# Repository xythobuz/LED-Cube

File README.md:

# 8x8x8 LED Cube

8x8x8 Single Color LED Cube built with an AtMega32.

## Building the Software

You need an AVR GCC Toolchain (eg. WinAVR) to compile both AVR firmwares. You need a C Compiler for your computer (only gcc tested, others should work) and a recent JDK with Java3D to build the PC Software, CubeControl. It should work on Windows, Mac OS X and Linux. To compile a project, just enter it's directory and run make. If you get errors compiling CubeControl, try changing the hard-coded JDK paths in the libSerial makefile, found in CubeControl/libSerial.

## Hardware

This LED-Cube uses an AtMega32 for displaying animations and an AtMega8 for Audio Visualizations. I first built the Circuit on a 160x100mm hole-grid board. This was very cumbersome, so I created a dual-sided PCB Layout with SMD Parts. You can find this Layout and the Schematic in the Hardware folder, as PNGs and Eagle files. There's also a partlist.

## Software

### CubeFirmware

CubeFirmware controls the AtMega32, which in turn displays images and communicates over USB. It's in the CubeFirmware folder. Compile with avr-gcc, using the makefile (just run 'make').

### AudioFirmware

This firmware controls the AtMega8, which interfaces the MSGEQ7 to get sound data. It is addressed by the CubeFirmware as a TWI-Slave. Compile it like CubeFirmware.

### CubeControl

CubeControl is a PC software, written in Java and mostly platform-independent, to create Animations for the Cube and send them to it. It depends on [Java3D](http://www.oracle.com/technetwork/java/javase/tech/index-jsp-138252.html) to display a rotatable, clickable 3D View of the LED-Cube. It comes with it's own Serial Library to communicate with the Cube. Compile it with the makefile. You need a working javac and gcc in your Path. To compile under windows get something like [MinGW](http://www.mingw.org/) or try Microsofts compiler.
A more or less recent Version of CubeControl can be found as CubeControl.jar. It includes a Mac and a Windows Version of the serial driver, so it is compatible with both of these platforms.

*Warning:* Java3D 1.5 is incompatible with more recent OS X versions and/or Java 7. [Possible workaround](https://github.com/hharrison/).

Also the Windows build of CubeControl is not tested very thoroughly. If you're on a 64bit Windows, you may also need to modify the libSerial makefile (add the `-m64` flag in the gcc call).

### HardwareEmulator

Allows you to test CubeControls up-/download capabilites. Unix only!

### UploadTest

Allows you to send test data or animations saved by CubeControl to the Cube. Unix only!

## License

See the included LICENSE file. This software is released as GPLv3. It incorporates some code from Peter Danneger (a [button debounce routine](http://www.mikrocontroller.net/articles/Entprellung#Debounce-Makro_von_Peter_Dannegger)) and Peter Fleury ([TWI Library](http://homepage.hispeed.ch/peterfleury/avr-software.html)).

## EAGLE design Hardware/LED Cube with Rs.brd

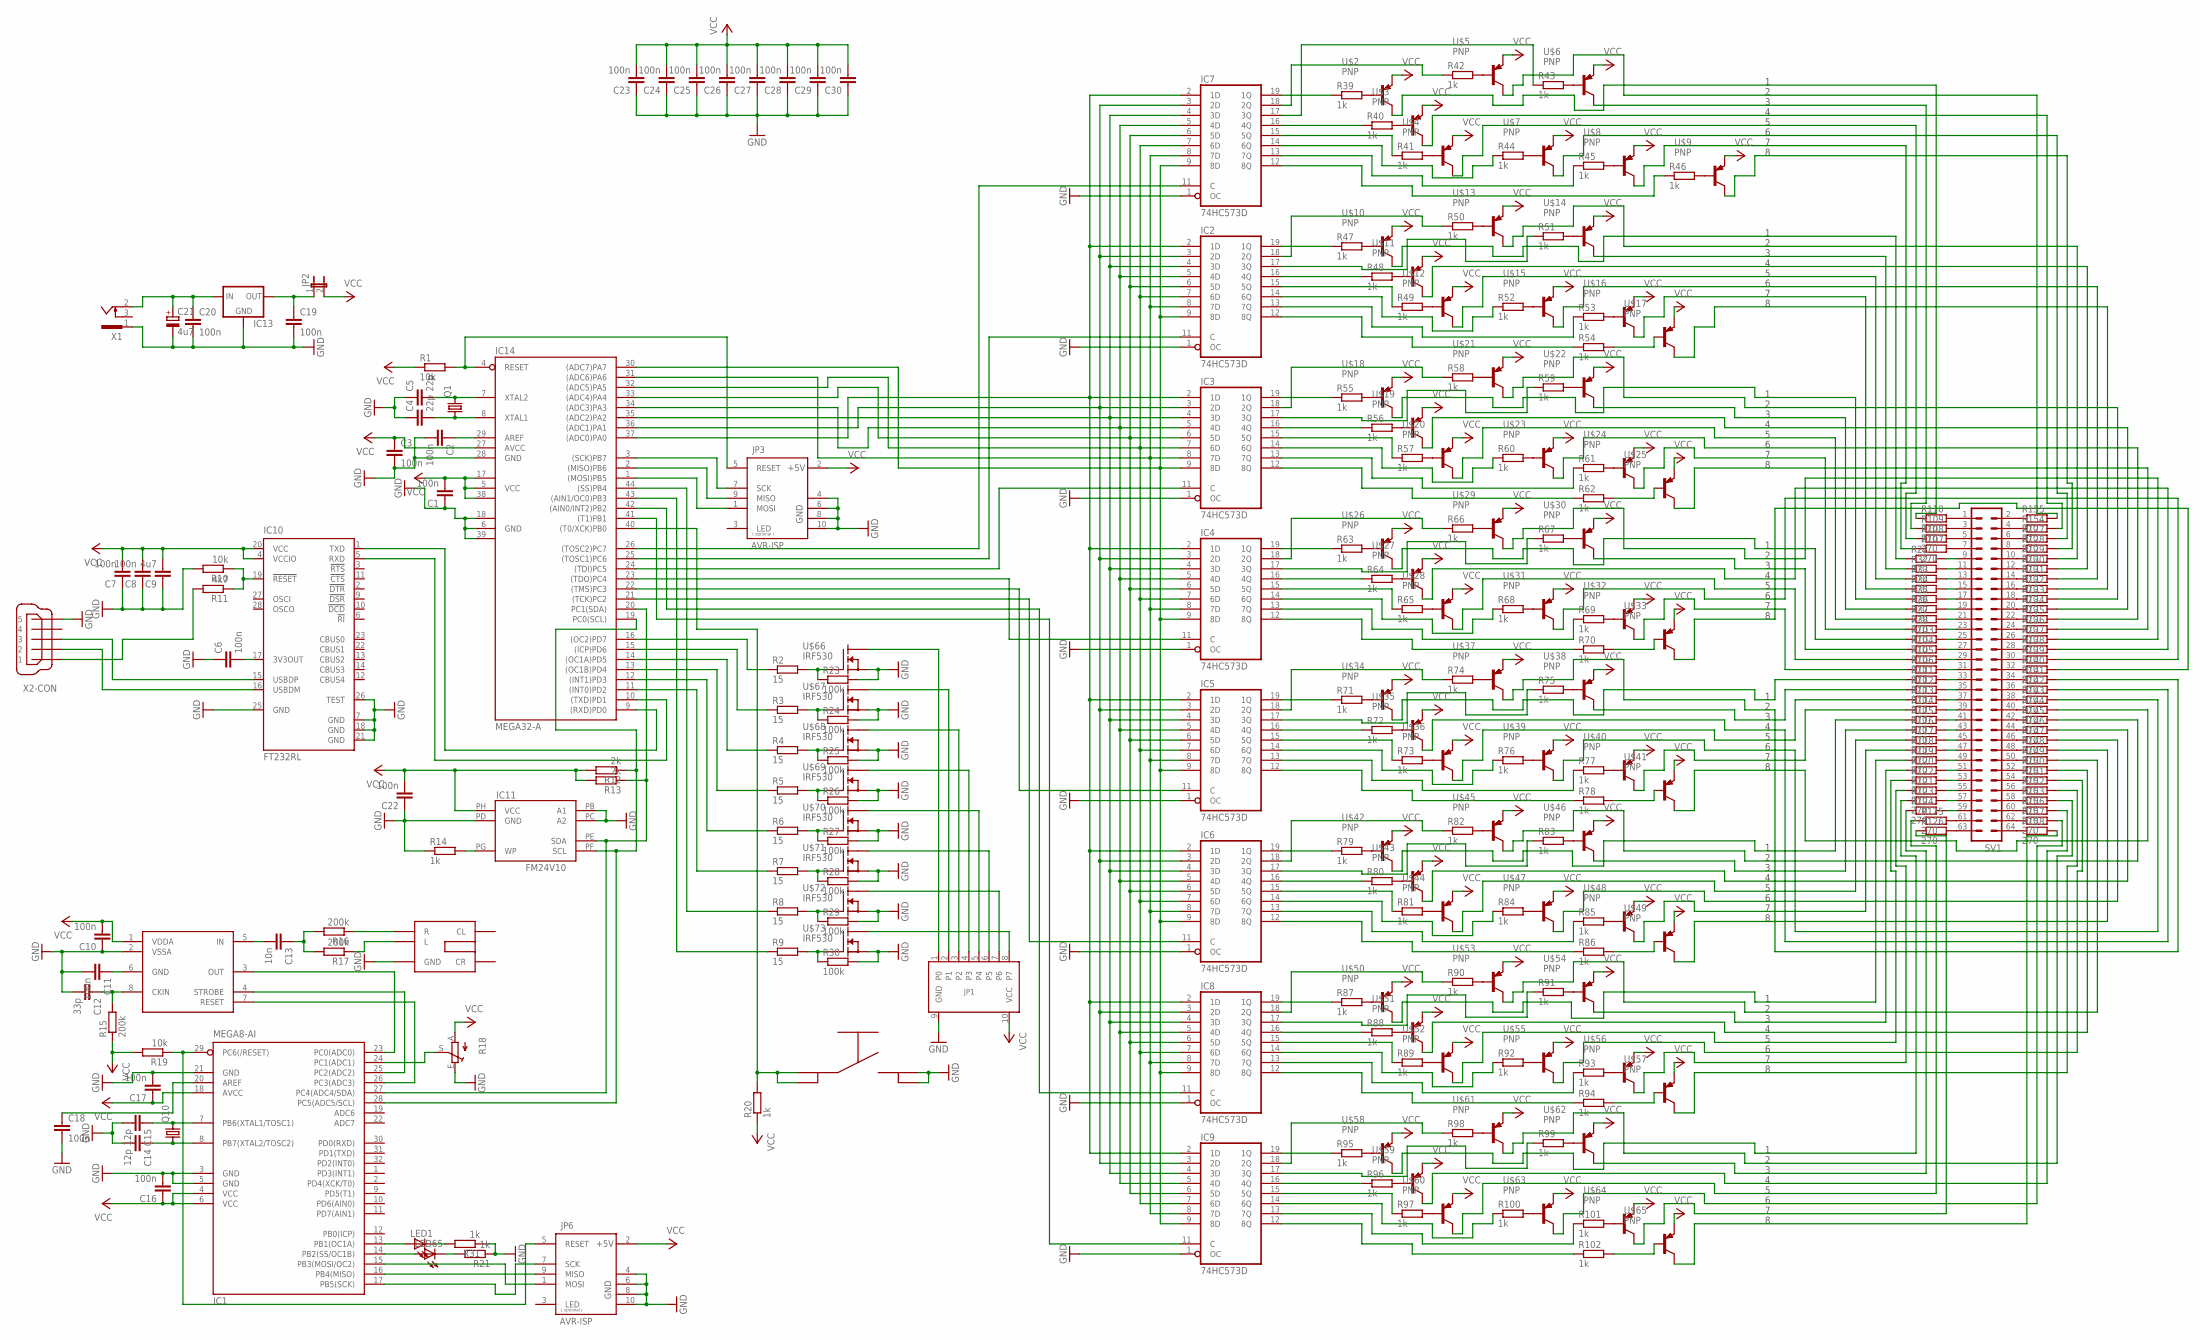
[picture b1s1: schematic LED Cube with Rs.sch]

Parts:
C1, C2, C3, C6, C7, C8, C10, C11, C16, C17, C18, C19, C20, C22, C23, C24, C25, C26, C27, C28, C29, C30: 100n; C0603
C4, C5: 22p; C0603
C9: 4u7; C0603
C12: 33p; C0603
C13: 10n; C0603
C14, C15: 12p; C0603
C21: 4u7; TAP5-80
IC1: MEGA8-AI; TQFP32-08
IC2, IC3, IC4, IC5, IC6, IC7, IC8, IC9: 74HC573D; SO20W
IC10: FT232RL; SSOP28
IC11: FM24V10; SOIC8
IC12: MSGEQ7; DIP8
IC13: 78XXS
IC14: MEGA32-A; TQFP44
JP1: PORT; ML10
JP2: JP1E; JP1
JP3, JP6: AVR-ISP; ML10
LED1, LED65: LEDCHIPLED_0603; CHIPLED_0603
Q1, Q10: CRYSTALHC49S; HC49/S
R1, R10, R19: 10k; R0603
R2, R3, R4, R5, R6, R7, R8, R9: 15; R0603
R11: 4k7; R0603
R12, R13: 2k; R0603
R14, R20, R21, R31, R39, R40, R41, R42, R43, R44, R45, R46, R47, R48, R49, R50, R51, R52, R53, R54, R55, R56, R57, R58, R59, R60, R61, R62, R63, R64, R65, R66, R67, R68, R69, R70, R71, R72, R73, R74, R75, R76, R77, R78, R79, R80, R81, R82, R83, R84, R85, R86, R87, R88, R89, R90, R91, R92, R93, R94, R95, R96, R97, R98, R99, R100, R101, R102: 1k; R0603
R15, R16, R17: 200k; R0603
R18: TRIM_EU-PT10S; PT-10S
R22, R32, R33, R34, R35, R36, R37, R38, R103, R104, R105, R106, R107, R108, R109, R110, R111, R112, R113, R114, R115, R116, R117, R118, R119, R120, R121, R122, R123, R124, R125, R126, R127, R128, R129, R130, R131, R132, R133, R134, R135, R136, R137, R138, R139, R140, R141, R142, R143, R144, R145, R146, R147, R148, R149, R150, R151, R152, R153, R154, R155, R156, R157, R158: 270; R0603
R23, R24, R25, R26, R27, R28, R29, R30: 100k; R0603
SV1: ML64
U$1: KLINKENBUCHSE; KLINKEPRINT
U$2, U$3, U$4, U$5, U$6, U$7, U$8, U$9, U$10, U$11, U$12, U$13, U$14, U$15, U$16, U$17, U$18, U$19, U$20, U$21, U$22, U$23, U$24, U$25, U$26, U$27, U$28, U$29, U$30, U$31, U$32, U$33, U$34, U$35, U$36, U$37, U$38, U$39, U$40, U$41, U$42, U$43, U$44, U$45, U$46, U$47, U$48, U$49, U$50, U$51, U$52, U$53, U$54, U$55, U$56, U$57, U$58, U$59, U$60, U$61, U$62, U$63, U$64, U$65: PNP; SOT323
U$66, U$67, U$68, U$69, U$70, U$71, U$72, U$73: IRF530; TO220-3V
U$74: TASTER; SMDTASTER
X1: 733980-62
X2: USB-B-MINI-SMD

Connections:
GND: C1.1, C2.2, C3.2, C4.1, C5.1, C6.1, C7.1, C8.1, C9.1, C10.1, C11.2, C12.2, C14.2, C15.2, C16.2, C17.2, C18.2, C19.2, C20.2, C21.-, C22.1, C23.1, C24.1, C25.1, C26.1, C27.1, C28.1, C29.1, C30.1, IC1.3 (GND), IC1.5 (GND), IC1.21 (GND), IC2.1 (OC), IC2.10 (GND), IC3.1 (OC), IC3.10 (GND), IC4.1 (OC), IC4.10 (GND), IC5.1 (OC), IC5.10 (GND), IC6.1 (OC), IC6.10 (GND), IC7.1 (OC), IC7.10 (GND), IC8.1 (OC), IC8.10 (GND), IC9.1 (OC), IC9.10 (GND), IC10.7 (GND), IC10.18 (GND), IC10.21 (GND), IC10.25 (GND), IC10.26 (TEST), IC11.PB (A1), IC11.PC (A2), IC11.PD (GND), IC12.2 (VSSA), IC13.GND, IC14.6 (GND), IC14.18 (GND1), IC14.28 (GND), IC14.39 (GND2), JP1.9 (GND), JP3.4 (GND), JP3.6 (GND), JP3.8 (GND), JP3.10 (GND), JP6.4 (GND), JP6.6 (GND), JP6.8 (GND), JP6.10 (GND), R10.2, R14.1, R18.E, R21.1, R23.2, R24.2, R25.2, R26.2, R27.2, R28.2, R29.2, R30.2, R31.1, U$1.GND, U$66.3 (S), U$67.3 (S), U$68.3 (S), U$69.3 (S), U$70.3 (S), U$71.3 (S), U$72.3 (S), U$73.3 (S), U$74.B, U$74.B2, X1.1, X2.5
unnamed: R154.2, U$3.P$3 (C)
unnamed: IC14.4 (RESET), JP3.5 (RESET), R1.2
unnamed: C2.1, IC14.29 (AREF)
unnamed: IC2.2 (1D), IC3.2 (1D), IC4.2 (1D), IC5.2 (1D), IC6.2 (1D), IC7.2 (1D), IC8.2 (1D), IC9.2 (1D), IC14.37 ((ADC0)PA0)
unnamed: IC2.3 (2D), IC3.3 (2D), IC4.3 (2D), IC5.3 (2D), IC6.3 (2D), IC7.3 (2D), IC8.3 (2D), IC9.3 (2D), IC14.36 ((ADC1)PA1)
unnamed: IC2.4 (3D), IC3.4 (3D), IC4.4 (3D), IC5.4 (3D), IC6.4 (3D), IC7.4 (3D), IC8.4 (3D), IC9.4 (3D), IC14.35 ((ADC2)PA2)
unnamed: C5.2, IC14.7 (XTAL2), Q1.2
unnamed: C4.2, IC14.8 (XTAL1), Q1.1
unnamed: IC2.5 (4D), IC3.5 (4D), IC4.5 (4D), IC5.5 (4D), IC6.5 (4D), IC7.5 (4D), IC8.5 (4D), IC9.5 (4D), IC14.34 ((ADC3)PA3)
unnamed: IC2.6 (5D), IC3.6 (5D), IC4.6 (5D), IC5.6 (5D), IC6.6 (5D), IC7.6 (5D), IC8.6 (5D), IC9.6 (5D), IC14.33 ((ADC4)PA4)
unnamed: IC2.7 (6D), IC3.7 (6D), IC4.7 (6D), IC5.7 (6D), IC6.7 (6D), IC7.7 (6D), IC8.7 (6D), IC9.7 (6D), IC14.32 ((ADC5)PA5)
unnamed: IC2.8 (7D), IC3.8 (7D), IC4.8 (7D), IC5.8 (7D), IC6.8 (7D), IC7.8 (7D), IC8.8 (7D), IC9.8 (7D), IC14.31 ((ADC6)PA6)
unnamed: IC2.9 (8D), IC3.9 (8D), IC4.9 (8D), IC5.9 (8D), IC6.9 (8D), IC7.9 (8D), IC8.9 (8D), IC9.9 (8D), IC14.30 ((ADC7)PA7)
unnamed: IC9.11 (C), IC14.41 ((T1)PB1)
unnamed: IC8.11 (C), IC14.42 ((AIN0/INT2)PB2)
unnamed: IC6.11 (C), IC14.21 ((TCK)PC2)
unnamed: IC5.11 (C), IC14.22 ((TMS)PC3)
unnamed: IC4.11 (C), IC14.23 ((TDO)PC4)
unnamed: IC3.11 (C), IC14.24 ((TDI)PC5)
unnamed: IC2.11 (C), IC14.25 ((TOSC1)PC6)
unnamed: IC7.11 (C), IC14.26 ((TOSC2)PC7)
unnamed: R2.2, R23.1, U$66.1 (G)
unnamed: IC14.16 ((OC2)PD7), R2.1
unnamed: IC14.15 ((ICP)PD6), R3.1
unnamed: IC14.14 ((OC1A)PD5), R4.1
unnamed: IC14.13 ((OC1B)PD4), R5.1
unnamed: IC14.12 ((INT1)PD3), R6.1
unnamed: IC14.11 ((INT0)PD2), R7.1
unnamed: IC14.44 ((SS)PB4), R8.1
unnamed: IC14.43 ((AIN1/OC0)PB3), R9.1
unnamed: R3.2, R24.1, U$67.1 (G)
unnamed: R4.2, R25.1, U$68.1 (G)
unnamed: R5.2, R26.1, U$69.1 (G)
unnamed: R6.2, R27.1, U$70.1 (G)
unnamed: R7.2, R28.1, U$71.1 (G)
unnamed: R8.2, R29.1, U$72.1 (G)
unnamed: R9.2, R30.1, U$73.1 (G)
unnamed: JP1.1 (P0), U$66.2 (D)
unnamed: JP1.2 (P1), U$67.2 (D)
unnamed: R106.2, SV1.31
unnamed: R105.2, SV1.29
unnamed: JP1.5 (P4), U$70.2 (D)
unnamed: JP1.6 (P5), U$71.2 (D)
unnamed: JP1.7 (P6), U$72.2 (D)
unnamed: JP1.8 (P7), U$73.2 (D)
unnamed: R11.2, X2.1
unnamed: IC14.3 ((SCK)PB7), JP3.7 (SCK)
unnamed: IC14.2 ((MISO)PB6), JP3.9 (MISO)
unnamed: IC14.1 ((MOSI)PB5), JP3.1 (MOSI)
unnamed: IC10.5 (RXD), IC14.10 ((TXD)PD1)
unnamed: IC10.1 (TXD), IC14.9 ((RXD)PD0)
unnamed: IC10.19 (!RESET), R10.1, R11.1
unnamed: IC1.27 (PC4(ADC4/SDA)), IC11.PE (SDA), IC14.20 (PC1(SDA)), R13.1
unnamed: IC10.15 (USBDP), X2.3
unnamed: C6.2, IC10.17 (3V3OUT)
unnamed: IC10.16 (USBDM), X2.2
unnamed: IC1.28 (PC5(ADC5/SCL)), IC11.PF (SCL), IC14.19 (PC0(SCL)), R12.1
unnamed: IC11.PG (WP), R14.2
unnamed: C12.1, IC12.8 (CKIN), R15.2
unnamed: C11.1, IC12.6 (GND)
unnamed: C13.2, IC12.5 (IN)
unnamed: C13.1, R16.2, R17.2
unnamed: R16.1, U$1.RIGHT (R)
unnamed: R17.1, U$1.LEFT (L)
unnamed: IC1.23 (PC0(ADC0)), IC12.3 (OUT)
unnamed: IC1.29 (PC6(/RESET)), JP6.5 (RESET), R19.1
unnamed: IC1.25 (PC2(ADC2)), IC12.4 (STROBE)
unnamed: IC1.26 (PC3(ADC3)), IC12.7 (RESET)
unnamed: IC14.40 ((T0/XCK)PB0), R20.2, U$74.A, U$74.A2
unnamed: C14.1, IC1.8 (PB7(XTAL2/TOSC2)), Q10.1
unnamed: C15.1, IC1.7 (PB6(XTAL1/TOSC1)), Q10.2
unnamed: R104.2, SV1.27
unnamed: R103.2, SV1.25
unnamed: C20.1, C21.+, IC13.IN, X1.2
unnamed: IC1.14 (PB2(SS/OC1B)), LED65.A
unnamed: LED65.C, R21.2
unnamed: IC1.24 (PC1(ADC1)), R18.S
unnamed: C18.1, IC1.20 (AREF)
unnamed: IC1.16 (PB4(MISO)), JP6.9 (MISO)
unnamed: IC1.15 (PB3(MOSI/OC2)), JP6.1 (MOSI)
unnamed: IC1.17 (PB5(SCK)), JP6.7 (SCK)
unnamed: LED1.C, R31.2
unnamed: IC1.13 (PB1(OC1A)), LED1.A
unnamed: C19.1, IC13.OUT, JP2.1
unnamed: R38.2, SV1.23
unnamed: R37.2, SV1.21
unnamed: R36.2, SV1.19
unnamed: R35.2, SV1.17
unnamed: R34.2, SV1.15
unnamed: R33.2, SV1.13
unnamed: R32.2, SV1.11
unnamed: R22.2, SV1.9
unnamed: R107.2, SV1.7
unnamed: R108.2, SV1.5
unnamed: R123.2, SV1.57
unnamed: R109.2, SV1.3
unnamed: R110.2, SV1.1
unnamed: R155.2, U$5.P$3 (C)
unnamed: R109.1, U$6.P$3 (C)
unnamed: R108.1, U$4.P$3 (C)
unnamed: R44.2, U$7.P$1 (B)
unnamed: R127.2, U$7.P$3 (C)
unnamed: R42.2, U$5.P$1 (B)
unnamed: R128.2, U$9.P$3 (C)
unnamed: R132.2, U$17.P$3 (C)
unnamed: R63.2, U$26.P$1 (B)
unnamed: R64.2, U$27.P$1 (B)
unnamed: R65.2, U$28.P$1 (B)
unnamed: R130.2, U$11.P$3 (C)
unnamed: R129.2, U$13.P$3 (C)
unnamed: R22.1, U$10.P$3 (C)
unnamed: R54.2, U$17.P$1 (B)
unnamed: IC4.19 (1Q), R63.1
unnamed: IC4.16 (4Q), R64.1
unnamed: R66.2, U$29.P$1 (B)
unnamed: IC4.18 (2Q), R66.1
unnamed: R67.2, U$30.P$1 (B)
unnamed: IC4.17 (3Q), R67.1
unnamed: IC4.15 (5Q), R65.1
unnamed: R68.2, U$31.P$1 (B)
unnamed: R71.2, U$34.P$1 (B)
unnamed: R72.2, U$35.P$1 (B)
unnamed: R73.2, U$36.P$1 (B)
unnamed: IC5.19 (1Q), R71.1
unnamed: IC5.16 (4Q), R72.1
unnamed: R74.2, U$37.P$1 (B)
unnamed: IC5.18 (2Q), R74.1
unnamed: R75.2, U$38.P$1 (B)
unnamed: IC7.19 (1Q), R39.1
unnamed: R126.1, U$64.P$3 (C)
unnamed: R125.1, U$60.P$3 (C)
unnamed: IC7.16 (4Q), R40.1
unnamed: IC2.19 (1Q), R47.1
unnamed: R157.2, U$63.P$3 (C)
unnamed: IC2.16 (4Q), R48.1
unnamed: R153.2, U$61.P$3 (C)
unnamed: R95.2, U$58.P$1 (B)
unnamed: R121.1, U$56.P$3 (C)
unnamed: R96.2, U$59.P$1 (B)
unnamed: R97.2, U$60.P$1 (B)
unnamed: IC9.19 (1Q), R95.1
unnamed: R151.2, U$55.P$3 (C)
unnamed: IC9.16 (4Q), R96.1
unnamed: R149.2, U$53.P$3 (C)
unnamed: R87.2, U$50.P$1 (B)
unnamed: R88.2, U$51.P$1 (B)
unnamed: R89.2, U$52.P$1 (B)
unnamed: IC8.16 (4Q), R88.1
unnamed: IC8.19 (1Q), R87.1
unnamed: R90.2, U$53.P$1 (B)
unnamed: IC8.18 (2Q), R90.1
unnamed: R91.2, U$54.P$1 (B)
unnamed: R79.2, U$42.P$1 (B)
unnamed: R80.2, U$43.P$1 (B)
unnamed: R81.2, U$44.P$1 (B)
unnamed: IC6.19 (1Q), R79.1
unnamed: IC6.16 (4Q), R80.1
unnamed: R82.2, U$45.P$1 (B)
unnamed: IC6.18 (2Q), R82.1
unnamed: R83.2, U$46.P$1 (B)
unnamed: R40.2, U$3.P$1 (B)
unnamed: R39.2, U$2.P$1 (B)
unnamed: IC7.15 (5Q), R41.1
unnamed: R110.1, U$2.P$3 (C)
unnamed: R41.2, U$4.P$1 (B)
unnamed: R107.1, U$8.P$3 (C)
unnamed: IC3.19 (1Q), R55.1
unnamed: IC3.16 (4Q), R56.1
unnamed: R47.2, U$10.P$1 (B)
unnamed: IC7.14 (6Q), R44.1
unnamed: R45.2, U$8.P$1 (B)
unnamed: IC7.18 (2Q), R42.1
unnamed: R43.2, U$6.P$1 (B)
unnamed: R48.2, U$11.P$1 (B)
unnamed: IC7.17 (3Q), R43.1
unnamed: IC7.13 (7Q), R45.1
unnamed: R46.2, U$9.P$1 (B)
unnamed: R49.2, U$12.P$1 (B)
unnamed: IC7.12 (8Q), R46.1
unnamed: R35.1, U$18.P$3 (C)
unnamed: R103.1, U$26.P$3 (C)
unnamed: IC4.14 (6Q), R68.1
unnamed: R33.1, U$12.P$3 (C)
unnamed: R50.2, U$13.P$1 (B)
unnamed: IC2.18 (2Q), R50.1
unnamed: R51.2, U$14.P$1 (B)
unnamed: IC2.17 (3Q), R51.1
unnamed: R32.1, U$14.P$3 (C)
unnamed: IC2.15 (5Q), R49.1
unnamed: R69.2, U$32.P$1 (B)
unnamed: IC4.13 (7Q), R69.1
unnamed: R52.2, U$15.P$1 (B)
unnamed: IC2.14 (6Q), R52.1
unnamed: R131.2, U$15.P$3 (C)
unnamed: R53.2, U$16.P$1 (B)
unnamed: IC2.13 (7Q), R53.1
unnamed: R34.1, U$16.P$3 (C)
unnamed: IC4.12 (8Q), R70.1
unnamed: R140.2, U$33.P$3 (C)
unnamed: IC2.12 (8Q), R54.1
unnamed: R55.2, U$18.P$1 (B)
unnamed: R56.2, U$19.P$1 (B)
unnamed: R57.2, U$20.P$1 (B)
unnamed: R111.1, U$34.P$3 (C)
unnamed: R115.1, U$42.P$3 (C)
unnamed: R58.2, U$21.P$1 (B)
unnamed: IC3.18 (2Q), R58.1
unnamed: R59.2, U$22.P$1 (B)
unnamed: IC3.17 (3Q), R59.1
unnamed: IC3.15 (5Q), R57.1
unnamed: R60.2, U$23.P$1 (B)
unnamed: IC3.14 (6Q), R60.1
unnamed: R61.2, U$24.P$1 (B)
unnamed: IC3.13 (7Q), R61.1
unnamed: IC3.12 (8Q), R62.1
unnamed: R136.2, U$25.P$3 (C)
unnamed: R38.1, U$24.P$3 (C)
unnamed: R135.2, U$23.P$3 (C)
unnamed: R37.1, U$20.P$3 (C)
unnamed: R134.2, U$19.P$3 (C)
unnamed: R133.2, U$21.P$3 (C)
unnamed: R119.1, U$50.P$3 (C)
unnamed: R62.2, U$25.P$1 (B)
unnamed: R36.1, U$22.P$3 (C)
unnamed: R106.1, U$32.P$3 (C)
unnamed: R139.2, U$31.P$3 (C)
unnamed: R105.1, U$28.P$3 (C)
unnamed: R138.2, U$27.P$3 (C)
unnamed: R137.2, U$29.P$3 (C)
unnamed: R123.1, U$58.P$3 (C)
unnamed: R70.2, U$33.P$1 (B)
unnamed: R104.1, U$30.P$3 (C)
unnamed: IC5.17 (3Q), R75.1
unnamed: IC5.15 (5Q), R73.1
unnamed: R76.2, U$39.P$1 (B)
unnamed: IC5.14 (6Q), R76.1
unnamed: R77.2, U$40.P$1 (B)
unnamed: IC5.13 (7Q), R77.1
unnamed: IC5.12 (8Q), R78.1
unnamed: R144.2, U$41.P$3 (C)
unnamed: R114.1, U$40.P$3 (C)
unnamed: R143.2, U$39.P$3 (C)
unnamed: R113.1, U$36.P$3 (C)
unnamed: R142.2, U$35.P$3 (C)
unnamed: R141.2, U$37.P$3 (C)
unnamed: R111.2, SV1.33
unnamed: R78.2, U$41.P$1 (B)
unnamed: R112.1, U$38.P$3 (C)
unnamed: IC6.17 (3Q), R83.1
unnamed: IC6.15 (5Q), R81.1
unnamed: R84.2, U$47.P$1 (B)
unnamed: IC6.14 (6Q), R84.1
unnamed: R85.2, U$48.P$1 (B)
unnamed: IC6.13 (7Q), R85.1
unnamed: IC6.12 (8Q), R86.1
unnamed: R148.2, U$49.P$3 (C)
unnamed: R118.1, U$48.P$3 (C)
unnamed: R147.2, U$47.P$3 (C)
unnamed: R117.1, U$44.P$3 (C)
unnamed: R146.2, U$43.P$3 (C)
unnamed: R145.2, U$45.P$3 (C)
unnamed: R112.2, SV1.35
unnamed: R86.2, U$49.P$1 (B)
unnamed: R116.1, U$46.P$3 (C)
unnamed: IC8.17 (3Q), R91.1
unnamed: IC8.15 (5Q), R89.1
unnamed: R92.2, U$55.P$1 (B)
unnamed: IC8.14 (6Q), R92.1
unnamed: R93.2, U$56.P$1 (B)
unnamed: IC8.13 (7Q), R93.1
unnamed: IC8.12 (8Q), R94.1
unnamed: R152.2, U$57.P$3 (C)
unnamed: R98.2, U$61.P$1 (B)
unnamed: IC9.18 (2Q), R98.1
unnamed: R122.1, U$52.P$3 (C)
unnamed: R150.2, U$51.P$3 (C)
unnamed: R99.2, U$62.P$1 (B)
unnamed: JP1.3 (P2), U$68.2 (D)
unnamed: R94.2, U$57.P$1 (B)
unnamed: R120.1, U$54.P$3 (C)
unnamed: IC9.17 (3Q), R99.1
unnamed: IC9.15 (5Q), R97.1
unnamed: R100.2, U$63.P$1 (B)
unnamed: IC9.14 (6Q), R100.1
unnamed: R101.2, U$64.P$1 (B)
unnamed: IC9.13 (7Q), R101.1
unnamed: IC9.12 (8Q), R102.1
unnamed: R158.2, U$65.P$3 (C)
unnamed: JP1.4 (P3), U$69.2 (D)
unnamed: R113.2, SV1.37
unnamed: R114.2, SV1.39
unnamed: R156.2, U$59.P$3 (C)
unnamed: R115.2, SV1.41
unnamed: R116.2, SV1.43
unnamed: R102.2, U$65.P$1 (B)
unnamed: R124.1, U$62.P$3 (C)
unnamed: R117.2, SV1.45
unnamed: R118.2, SV1.47
unnamed: R119.2, SV1.49
unnamed: R120.2, SV1.51
unnamed: R122.2, SV1.53
unnamed: R121.2, SV1.55
unnamed: R124.2, SV1.59
unnamed: R125.2, SV1.61
unnamed: R126.2, SV1.63
unnamed: R127.1, SV1.6
unnamed: R128.1, SV1.8
unnamed: R129.1, SV1.10
unnamed: R130.1, SV1.12
unnamed: R131.1, SV1.14
unnamed: R132.1, SV1.16
unnamed: R133.1, SV1.18
unnamed: R134.1, SV1.20
unnamed: R135.1, SV1.22
unnamed: R136.1, SV1.24
unnamed: R137.1, SV1.26
unnamed: R138.1, SV1.28
unnamed: R139.1, SV1.30
unnamed: R140.1, SV1.32
unnamed: R141.1, SV1.34
unnamed: R142.1, SV1.36
unnamed: R143.1, SV1.38
unnamed: R144.1, SV1.40
unnamed: R145.1, SV1.42
unnamed: R146.1, SV1.44
unnamed: R147.1, SV1.46
unnamed: R148.1, SV1.48
unnamed: R149.1, SV1.50
unnamed: R150.1, SV1.52
unnamed: R151.1, SV1.54
unnamed: R152.1, SV1.56
unnamed: R153.1, SV1.58
unnamed: R154.1, SV1.4
unnamed: R155.1, SV1.2
unnamed: R156.1, SV1.60
unnamed: R157.1, SV1.62
unnamed: R158.1, SV1.64
VCC: C1.2, C3.1, C7.2, C8.2, C9.2, C10.2, C16.1, C17.1, C22.2, C23.2, C24.2, C25.2, C26.2, C27.2, C28.2, C29.2, C30.2, IC1.4 (VCC), IC1.6 (VCC), IC1.18 (AVCC), IC2.20 (VCC), IC3.20 (VCC), IC4.20 (VCC), IC5.20 (VCC), IC6.20 (VCC), IC7.20 (VCC), IC8.20 (VCC), IC9.20 (VCC), IC10.4 (VCCIO), IC10.20 (VCC), IC11.PH (VCC), IC12.1 (VDDA), IC14.5 (VCC), IC14.17 (VCC1), IC14.27 (AVCC), IC14.38 (VCC2), JP1.10 (VCC), JP2.2, JP3.2 (+5V), JP6.2 (+5V), R1.1, R12.2, R13.2, R15.1, R18.A, R19.2, R20.1, U$2.P$2 (E), U$3.P$2 (E), U$4.P$2 (E), U$5.P$2 (E), U$6.P$2 (E), U$7.P$2 (E), U$8.P$2 (E), U$9.P$2 (E), U$10.P$2 (E), U$11.P$2 (E), U$12.P$2 (E), U$13.P$2 (E), U$14.P$2 (E), U$15.P$2 (E), U$16.P$2 (E), U$17.P$2 (E), U$18.P$2 (E), U$19.P$2 (E), U$20.P$2 (E), U$21.P$2 (E), U$22.P$2 (E), U$23.P$2 (E), U$24.P$2 (E), U$25.P$2 (E), U$26.P$2 (E), U$27.P$2 (E), U$28.P$2 (E), U$29.P$2 (E), U$30.P$2 (E), U$31.P$2 (E), U$32.P$2 (E), U$33.P$2 (E), U$34.P$2 (E), U$35.P$2 (E), U$36.P$2 (E), U$37.P$2 (E), U$38.P$2 (E), U$39.P$2 (E), U$40.P$2 (E), U$41.P$2 (E), U$42.P$2 (E), U$43.P$2 (E), U$44.P$2 (E), U$45.P$2 (E), U$46.P$2 (E), U$47.P$2 (E), U$48.P$2 (E), U$49.P$2 (E), U$50.P$2 (E), U$51.P$2 (E), U$52.P$2 (E), U$53.P$2 (E), U$54.P$2 (E), U$55.P$2 (E), U$56.P$2 (E), U$57.P$2 (E), U$58.P$2 (E), U$59.P$2 (E), U$60.P$2 (E), U$61.P$2 (E), U$62.P$2 (E), U$63.P$2 (E), U$64.P$2 (E), U$65.P$2 (E)

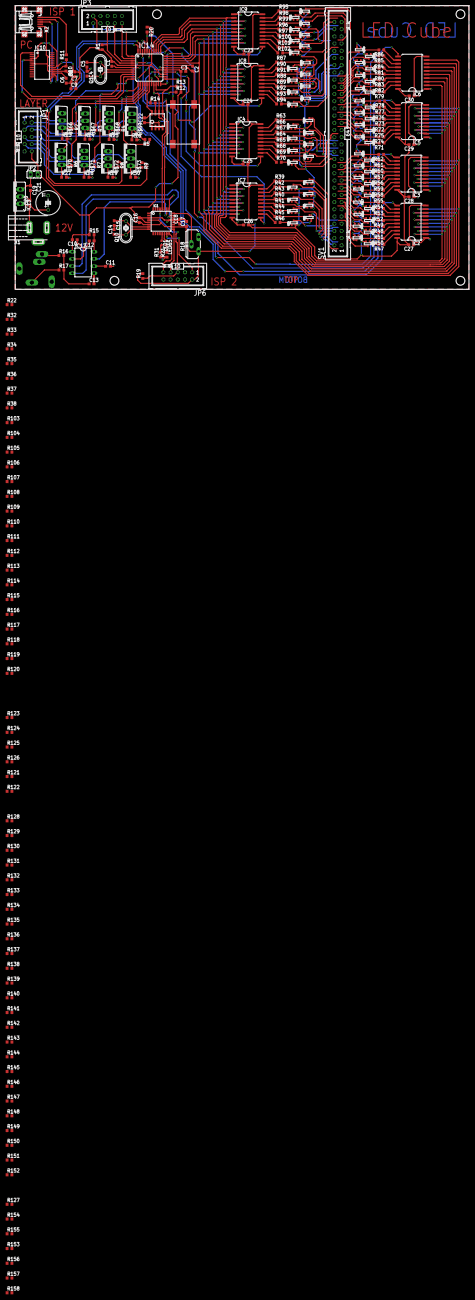
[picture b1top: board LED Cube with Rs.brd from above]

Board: 2 copper layers, 160.0 x 100.0 mm, 287 parts (1 on the bottom side), 339 nets.

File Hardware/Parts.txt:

Partlist

Quant.	Value			Device

22		100nF			0603
4		22pF			0603
1		4u7F			0603
1		33pF			0603
1		10nF			0603
1		100uF			CPOL-80

8		15R				0603
3		10kR			0603
8		100kR			0603
67		1kR				0603
3		200kR			0603
2		2kR				0603
1		4k7R			0603
64		120R			0603

64		PNP				BC 860CW
8		IRF530			IRF530
8		74HC573D		74HC573D
1		MEGA8-AI		MEGA8-AI
1		FT232RL			FT232RL
1		FM24V10			FM24V10
1		MSGEQ7			MSGEQ7
1		7805			78XXS
1		MEGA32-A		MEGA32-A

1		POTI			TRIM_EU-PT
1		Connector		ML64
1		Klinkenbuchse	Klinkenbuchse
1		TASTER			TASTER	SMD
1		DC-Stecker		733980-62
1		USB-B mini		USB-B-MINI-SMD

==>	48,63€
	Reichelt:
	https://secure.reichelt.de/index.html?;ACTION=20;AWKID=538158;PROVID=2084

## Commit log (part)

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2011-10-27 Added Copyright
2011-11-14 Added Initial Cube Control Source
2011-11-14 Added Copyright Notice
2011-11-14 Added Frame functionality
2011-11-14 Fixed gitignore...
2011-11-16 Fixed notification
2011-11-16 Test
2011-11-16 Added unix helper, makefile, deleted jfm
2011-11-16 Added Windows helper
2011-11-16 Helpers in one file
2011-11-17 Fixed winSerial.c
2011-11-17 All Layer Buttons now call the LayerEdit Frame LEDButtons now with color instead of images...
2011-11-17 Fixed makefile...
2011-11-17 Changed back to images... (thank to OS X)
2011-11-17 Clicking the LED-Buttons now actually changes the xolor of the button.
2011-11-17 The save dialog for the layeredit will now only appear if unsaved changes have been made
2011-11-17 Fixed makefile
2011-11-17 Makefile fix
2011-11-17 Added MyListsSelectionListener
2011-11-18 Added open/save dialog
2011-11-18 Added 3D Canvas
2011-11-18 Worked at cubeWorker...
2011-11-18 Worker can save now
2011-11-19 Renamed the Frame.class to AFrame.class to avoid compatibility issues on Windows. Note: the makefile now won't work! (Yep, I DID change it in there, too!)
2011-11-20 Fixed bugs in frame and created some new ones....
2011-11-21 Changed windows' serial timeout...
2011-11-22 ficed stupid bug in frame.java, which cleared all animation when you clicked on the "add animation" also fixed makefile for windows
2011-11-22 fixed bug in winSerial.c
2011-11-22 Fixed load/save
2011-11-22 Fixed Layereditor
2011-11-22 Added Animation rename
2011-11-23 Fixed editLayerFrame
2011-11-23 Fixed layer edit again, and again, and again...
2011-11-23 Fixed bug in layerEditor (surprise....)
2011-11-23 Enabled editing for every layer, not only the first one...
2011-11-23 Helper reads and lists ports
2011-11-24 Worker tries to use helper
2011-11-26 Small bugfixing in frame.java
2011-11-29 Worked at 3D stuff
2011-11-30 Made LEDs white and bright
2011-11-30 Worked at 3D stuff...
2011-11-30 Fixed merge errors
2011-12-04 Added debug console
2011-12-04 Added documentation
2011-12-05 Update 3D-View when layer is changed
2011-12-05 Removed unused methods
2011-12-05 oops...
2011-12-05 renamed 'frame' to 'Frame'
2011-12-05 Rename frame to Frame complete
2011-12-05 Fixing filename...
2011-12-05 Filename fixed...
2011-12-05 Removed unneeded groups
2011-12-05 3D now pretty :)
2011-12-05 Start helper from debug menu
2011-12-06 Added method to worker API
2011-12-06 Added FRAM to schematic
2011-12-07 Fixed makefile, renamed cryptical variables, set the default close operation
2011-12-07 Fixed makefile to death.....
2011-12-10 Added Splashscreen... (2 min of work, inclusive googling!)
2011-12-11 Added twi library
2011-12-11 New Splash png
2011-12-11 Added switch
2011-12-12 Beauty fixes...
2011-12-12 Attiny now Atmega
2011-12-13 Worked at cube low level code
2011-12-14 Fixed bug while loading from a file
2011-12-14 Removed the doc, also removed dependency from makefile
2011-12-15 Debugging firmware
2011-12-16 Now with nicer makefiles, auto OS detection
2011-12-16 Fixed unixSerial
2011-12-16 Tried to fix makefile...
2011-12-16 Fix again.... still not working
2011-12-16 Fixed makefile for windows...
2011-12-16 Debugging serial
2011-12-16 Listing serial ports in unix working
2011-12-17 Fixed the DLL creation on windows....
2011-12-17 Removed scanning delay
2011-12-17 Revert "ArrayList now LinkedList"
    This reverts commit 1c43cd23992a6084f778aed6b9300c6e1be68d30.
2011-12-17 Actually a bad idea...
2011-12-17 Nice makefile
2011-12-18 Library in jar now
2011-12-27 Added AudioFirmware
2011-12-31 Source now pretty
2011-12-31 Removed Eclipse Project files again
2012-01-10 Added Fullscreen (kinda)
    Fullscreen button, creates empty fullscreen JFrame
2012-01-10 Worked at audio firmware
2012-01-11 added missing "exit fullscreen"
2012-01-11 Audio detection working
2012-01-12 Made Fullscreen almost working….
2012-01-13 Added LEDs to Audio Device
2012-01-13 Fixed background in fullscreen mode...
2012-01-16 Fixed fullscreen rendering...
    … almost...
2012-01-16 Added Projektspezifikation
2012-01-22 added rudimentary "play animation"...
2012-01-22 tops… cleaned up...
2012-01-22 "play animation" now pauses the correct number of milliseconds
2012-01-26 Added Audio TWI Slave functionality
2012-01-27 Audio FW complete. New libs for Cube FW.
2012-01-30 Fullscreen now working
2012-01-30 Schematic fix
2012-02-01 Started layouting
2012-02-01 Worked at Layout
2012-02-02 Finished Layout
2012-02-02 Ordered PCB
2012-02-07 Can now send animations to cube.
2012-02-08 Upload download
2012-02-09 Worked at movement
2012-02-12 Worked at movement...
2012-02-12 Linux makefile
2012-02-12 Linux compatibility...
2012-02-16 Cube can receive animations
2012-02-17 Can now transmit animations
2012-02-17 Whoopsy...
2012-02-17 Fixed windows serial port detection
2012-02-20 Fixed movement
2012-02-22 wtf… hiilfe… git spackt grad...
2012-02-22 aaah
2012-02-29 Fixed Frame / Anim movement
2012-02-29 Added avr binarys
2012-02-29 Added docs
2012-03-01 Fixed Layout
2012-03-04 New UI
2012-03-04 Fixed syntax error in new UI
2012-03-04 Fixed horrible code style
2012-03-05 Fix GUI
2012-03-06 Cleaned up
    Fixed crappy indents again. Fixed editButton Creation.
2012-03-07 Now compiles on Mac
2012-03-07 3D now optionable
2012-03-07 Reactivated 3D
    Accidentally left 3D Stuff as comment…
2012-03-07 Fixed windows problems!
    Finally! It's working… The DLL did not follow the _stdcall naming
    convention!
2012-03-11 LEDs nearly selectable :)
    All the code that we need to select a LED with the mouse is there…
    Unfortunately, we have a "CapabilityNotSetException" and i don't know
    where to set that capability… See Led3D.java Line 198!
2012-03-11 Now not comparing Bounds but comparing objects.
    Unfortunately, the Class.equals() seems to compare something that
    differs between our stored LED Spheres and the Clicked Primitive… Need
    to find another way to compare…
2012-03-11 Replaced serial Library.
    This was done because I was suspecting an error to be there. This is
    not the case, so we probably have a Hardware Problem with our USB
    Serial Stuff… If we send data too fast it sends garbage. It also always
    sends two additional bytes (0xC2 at the beginning, 0xFF at the end),
    which both come at the beginning if we don't delay between sending the
    chars…
2012-03-11 Debugging
2012-03-12 Fixed duration (hutattedonmyarm), fixed playing (hutattedonmyarm), fixed other stuff (xythobuz)
2012-03-15 Added slider for setting frame duration
2012-03-15 Fixed some frame stuff.
    Auto select animations and frames, consistent order for frame and
    animation buttons.
2012-03-18 CubeFirmware debug mode improvements.
    Now talks to FRAM most of the time…
2012-03-18 Screwed around in the extendArray(), because it didn't work sometimes...
    What the....? Well it works THIS way...
2012-03-18 Code beautification…
2012-03-18 Consistent storage format.
    No longer using one- and two-dimensional arrays combined.
2012-03-19 Made LEDs clickable... (kind of...)
2012-03-23 Created Hardware Emulator.
    Runs on Unix and creates a virtual serial port that can be opened by
    CubeControl. Only responds to OK, (h)elp and (v)ersion right now.
2012-03-26 Added Protocol description as pdf.
    Take a look at this to understand the protocol between hard- and
    software.
2012-03-27 Removed font. It was the default one.
2012-03-27 Added pseudo logo.
2012-03-27 Added 3d snake game to play on cube.
    Yes, I'm bored. But thats only for you to do the real work *wink wink*…
2012-03-28 Fixed legs
2012-03-28 Fixed some element sizes.
2012-03-28 Fixed levs, added axis and center point
2012-03-28 *cough* whoopsy
2012-04-01 Selecting LEDs now works perfectly!
2012-04-01 Fixed wrong translation data in resetView(), also added fullscreen detection for resetView(), and made nicer viewing point in fullscreen
2012-04-12 Fixed Renamebug
2012-04-13 Fixed horrible syntax.
    Honestly: What is this kind of shit? Do you even care the slightest bit?
2012-04-13 Strings now in program memory.
2012-04-16 Fixed bug in fullscreenplayer, renamed animationfileextension to .cube
2012-04-17 misc changes
2012-04-18 Cube now flicker free.
    The display now gets updated with 48fps or 384 layers per second, while
    the animations still play with 24fps.
2012-04-18 Fixed label of toggleLegsButton
2012-04-18 Fixed coordinate axis
2012-04-18 Revert "aaah..."
    This reverts commit b6b00a6bcdfbe319acfe659ec4306de9b5710ad5.
2012-04-19 Removed vim bugger file *whoopsy* and added toggleLegsButton to fullscreenmode
2012-04-24 Added random animation.
2012-04-26 Fixed legs not rotating while not being displayed
2012-05-14 Fixed latch selection
    Code never was rewritten for new Hardware.
2012-05-17 Misc Firmware fixes.
    Audio Firmware now with Watchdog. Removed unused code. Fixed compiler
    warnings. Fixed cube coordinate system problems. Fixed audio display
    rotation. Nicer Idle Display with SAP Logo. Increased Firmware Version
    Number. Debug Build even more talky.
2012-05-20 Misc work.
    Changed some more faulty transistors. cubeInit now displays short test
    animation. Moved header files in own folder.
2012-05-23 nicer fullscreen (still in progress)
2012-05-23 Misc fixes.
    Audio CPU now resets MSGEQ7 properly. Bufferhelper clears memory after
    allocation. Z Axis now goes into the correct direction. Removed
    FillRect. Enabled Watchdog for Debug Build, too. Removed unneeded
    strings. Built-In Framedata in own file. Makefile cleans object files
    after every build, because it doesn't matter. Simple Visualization
    works correctly. Most recent Hex-Files now included.
2012-05-27 Removes unnecessary output
2012-05-27 White background
2012-05-28 Misc fixes.
    Better error output CubeControl. Better debug output cubeEmu. cubeEmu
    now supports sending data, but still hangs sometimes or doesn't answer
    with OKs, etc.
2012-05-28 Added animation which will later be hardcoded
2012-05-28 Misc changes to FW
2012-05-28 Can now always kill emulator with ctrl+c
2012-05-28 Forgot another ack in emu.
2012-05-28 Fixed off by one errors…
2012-05-28 Started implementing download
2012-05-28 continued implementing the download function
2012-05-28 Fixed download in emulator.
2012-06-01 Moved receive and transmit routines.
2012-06-08 Started hardcoding an animation
2012-06-08 Fucked up file access rights.
2012-06-08 Fixed Winavr compiler error.
2012-06-08 Off-by-One bug.
2012-06-08 Fixed errors.
2012-06-09 Some AudioFirmware fixes.
    Rewrote MSGEQ7 Algorithm. Removed stdlib.h dependency, thereby reducing
    the flash needed by 50%. Interrupts no longer enabled in twislave, but
    in main.
2012-06-10 Fixed animations.
2012-06-11 Finished hardcoding animation and deleted the ugly part of it
2012-06-11 Splitted Animation
2012-06-16 Added Upload Utility.
2012-06-17 CubeWorker is sending data!
2012-06-21 Misc. fixes.
    Poti is now a multiplication, from 1 to 3,5. Also added basic noise
    filtering. UploadTest can now send a specific byte as frame data.
2012-06-21 Can now cycle through different audio visualizations with button.
    Also better filtering for audio data in AudioFirmware.
2012-06-22 Built new LED Cube, implemented Lookup Table to compensate for shitty connections.
2012-06-22 Removed Debug build
2012-06-23 CubeFirmware major rewrite.
    Removed buggy idle animations. Killed idle frames alltogether.
2012-06-23 Implemented Audio Mode again.
    Beware: freeing static, unallocated memory will cause very strange
    behavior!
2012-06-24 removed axis
2012-06-24 Logarithmic scale visualizer implemented.
2012-06-24 Improved Visualizer.
2012-06-24 Misc changes.
    Reversed button scroll direction, removed cruft, linLog Visualization
    is now started after boot. Revised filter for audio data.
2012-06-25 Can now upload frames "by hand"
2012-06-25 Storing frames no longer corrupts them!
2012-06-26 Improved Readme.
2012-06-27 Extended Readme.
2012-06-28 Can render text.
    Font is not pretty, but works :)
2012-06-29 Fixed frame counter width.
    Only used 8bit vars, while 16bit were required.
2012-07-08 Extended new font.
2012-07-08 Added Crossplatform CubeControl
2012-07-14 '?' now prints version instead of help.
2013-01-11 Refrmatted Partlist.
2013-10-21 Modified Readme
2016-03-28 Alternative for FRAM IC
